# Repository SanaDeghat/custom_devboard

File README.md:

# custom_devboard

what? I made a devboard, which I creativly named devboard hehehhe

Why? My friend really insisted i learn how to lol, and also i rly wnat mroe jellycats so i gotta WORK yk??

How? I used Kicad, Did everything from the PCB to schematics all of it and i drew with clip studio paint (look in my devlog for details) 

What you struggled with and what you learned? OMG I LEARNED TAHT U CAN USE THE FILLY THING TO CONNECT STUFF (Zone fill) I think i would have had a mental breakdown if I had to connect all the GDN.

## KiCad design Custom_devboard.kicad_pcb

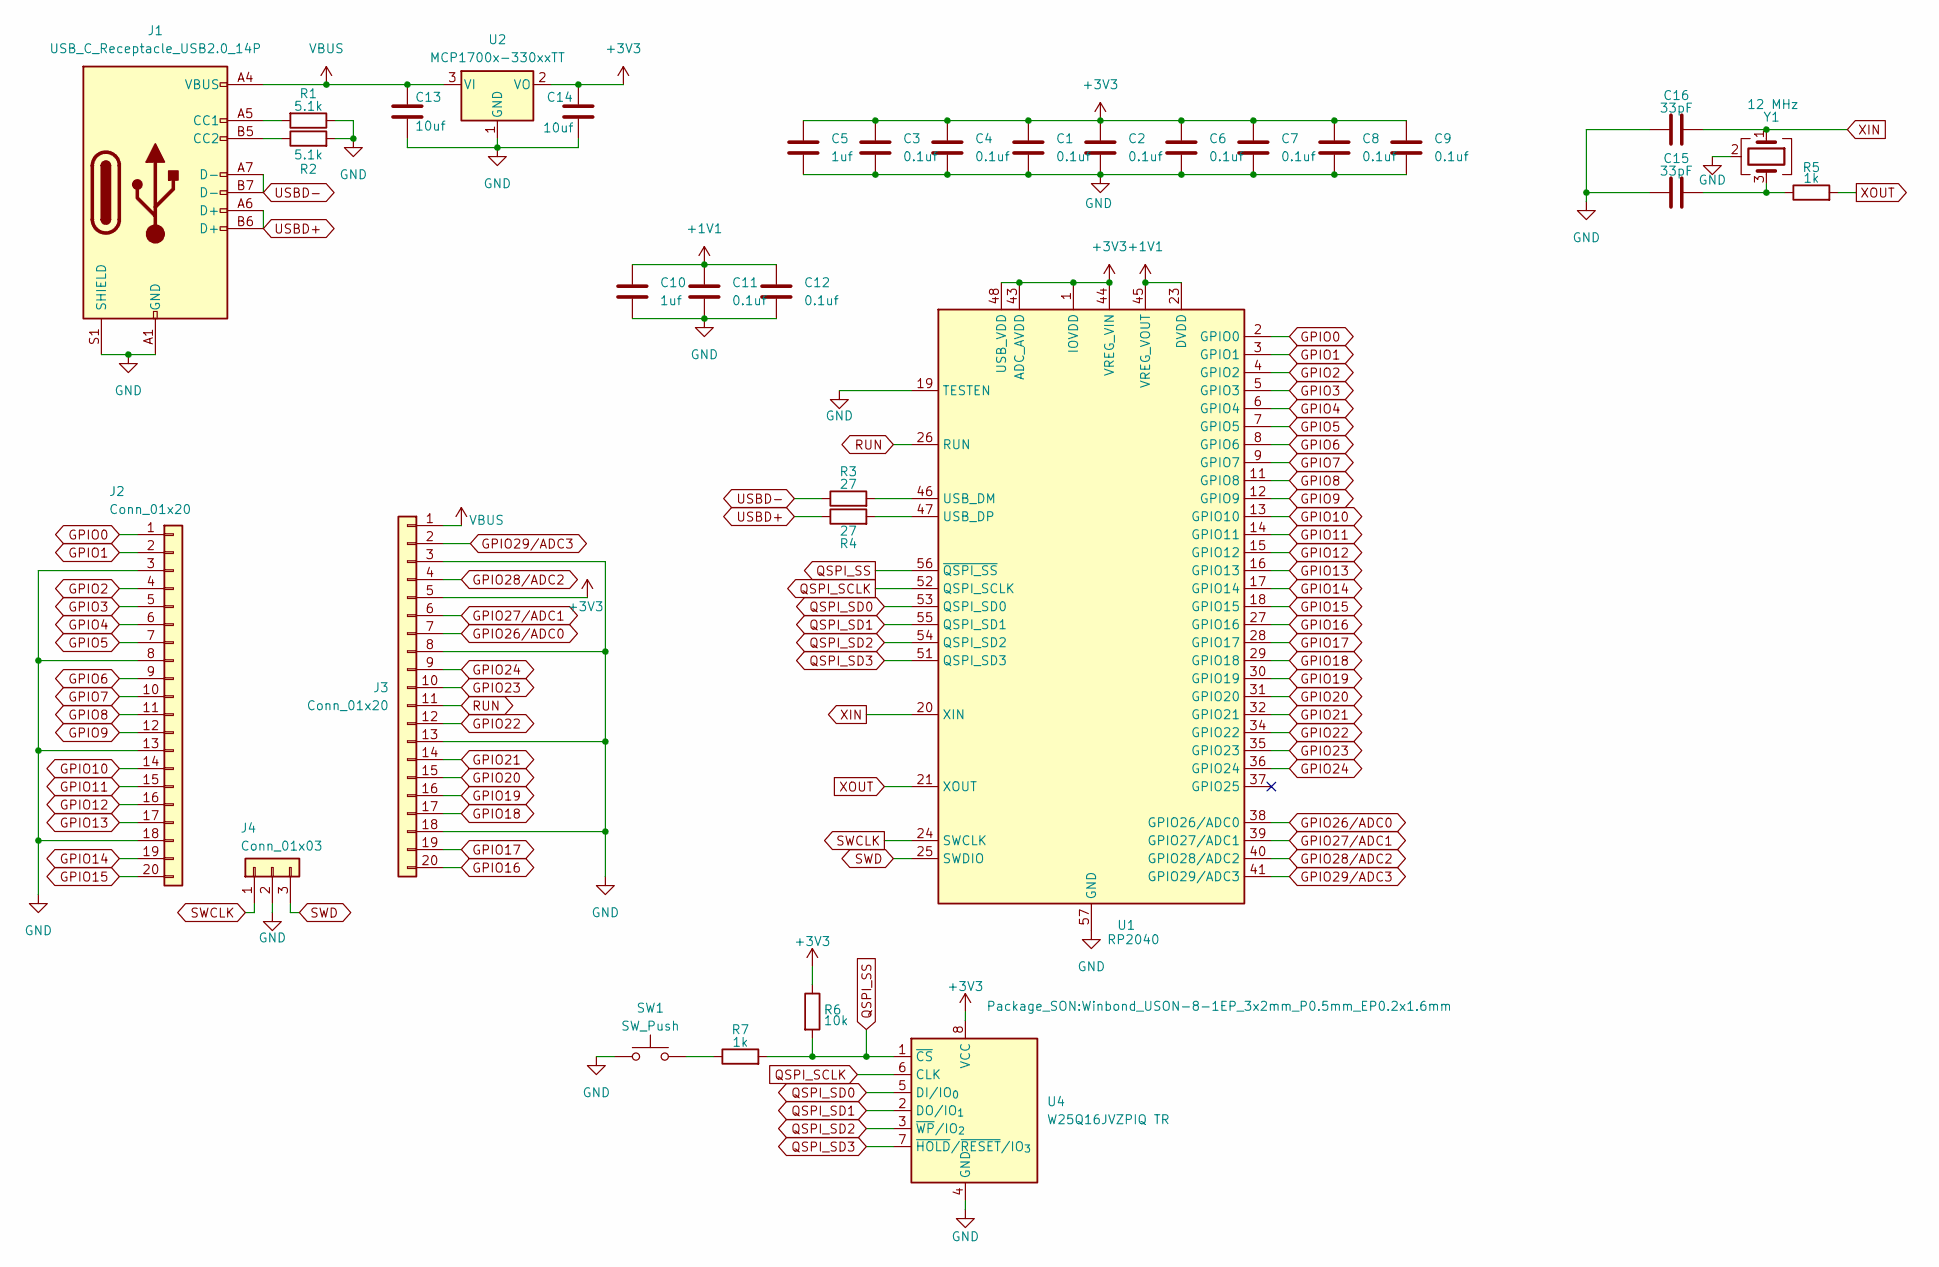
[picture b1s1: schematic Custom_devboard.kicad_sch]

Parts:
C1, C2, C3, C4, C6, C7, C8, C9, C11: 0.1uf; C_0402_1005Metric
C5, C10: 1uf; C_0402_1005Metric
C12: 0.1uf; C_0201_0603Metric
C13, C14: 10uf; C_0201_0603Metric
C15, C16: 33pF; C_0201_0603Metric
J1: USB_C_Receptacle_USB2.0_14P; USB_C_Receptacle_HRO_TYPE-C-31-M-12
J2, J3: Conn_01x20; PinHeader_1x20_P2.54mm_Vertical
J4: Conn_01x03; PinHeader_1x03_P2.54mm_Vertical
R1, R2: 5.1k; R_0402_1005Metric
R3, R4: 27; R_0402_1005Metric
R5, R7: 1k; R_0402_1005Metric
R6: 10k; R_0402_1005Metric
SW1: SW_Push; SW_Push_SPST_NO_Alps_SKRK
U1: RP2040; QFN-56-1EP_7x7mm_P0.4mm_EP3.2x3.2mm
U2: MCP1700x-330xxTT; SOT-23
U4: W25Q16JVZPIQ TR; Winbond_USON-8-1EP_3x2mm_P0.5mm_EP0.2x1.6mm
Y1: 12 MHz; Crystal_SMD_3225-4Pin_3.2x2.5mm

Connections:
+1V1: C10.1, C11.1, C12.1, U1.23 (DVDD), U1.45 (VREG_VOUT), U1.50 (DVDD)
+3V3: C1.1, C2.1, C3.1, C4.1, C5.1, C6.1, C7.1, C8.1, C9.1, C14.1, J3.5, R6.1, U1.1 (IOVDD), U1.10 (IOVDD), U1.22 (IOVDD), U1.33 (IOVDD), U1.42 (IOVDD), U1.43 (ADC_AVDD), U1.44 (VREG_VIN), U1.48 (USB_VDD), U1.49 (IOVDD), U2.2 (VO), U4.8 (VCC)
GND: C1.2, C2.2, C3.2, C4.2, C5.2, C6.2, C7.2, C8.2, C9.2, C10.2, C11.2, C12.2, C13.2, C14.2, C15.1, C16.1, J1.A1 (GND), J1.A12 (GND), J1.B1 (GND), J1.B12 (GND), J1.S1 (SHIELD), J2.3, J2.8, J2.13, J2.18, J3.3, J3.8, J3.13, J3.18, J4.2, R1.1, R2.2, SW1.1, U1.19 (TESTEN), U1.57 (GND), U2.1 (GND), U4.4 (GND), Y1.2 (G), Y1.4 (G)
GPIO0: J2.1, U1.2 (GPIO0)
GPIO1: J2.2, U1.3 (GPIO1)
GPIO2: J2.4, U1.4 (GPIO2)
GPIO3: J2.5, U1.5 (GPIO3)
GPIO4: J2.6, U1.6 (GPIO4)
GPIO5: J2.7, U1.7 (GPIO5)
GPIO6: J2.9, U1.8 (GPIO6)
GPIO7: J2.10, U1.9 (GPIO7)
GPIO8: J2.11, U1.11 (GPIO8)
GPIO9: J2.12, U1.12 (GPIO9)
GPIO10: J2.14, U1.13 (GPIO10)
GPIO11: J2.15, U1.14 (GPIO11)
GPIO12: J2.16, U1.15 (GPIO12)
GPIO13: J2.17, U1.16 (GPIO13)
GPIO14: J2.19, U1.17 (GPIO14)
GPIO15: J2.20, U1.18 (GPIO15)
GPIO16: J3.20, U1.27 (GPIO16)
GPIO17: J3.19, U1.28 (GPIO17)
GPIO18: J3.17, U1.29 (GPIO18)
GPIO19: J3.16, U1.30 (GPIO19)
GPIO20: J3.15, U1.31 (GPIO20)
GPIO21: J3.14, U1.32 (GPIO21)
GPIO22: J3.12, U1.34 (GPIO22)
GPIO23: J3.10, U1.35 (GPIO23)
GPIO24: J3.9, U1.36 (GPIO24)
GPIO26/ADC0: J3.7, U1.38 (GPIO26/ADC0)
GPIO27/ADC1: J3.6, U1.39 (GPIO27/ADC1)
GPIO28/ADC2: J3.4, U1.40 (GPIO28/ADC2)
GPIO29/ADC3: J3.2, U1.41 (GPIO29/ADC3)
unnamed: C15.2, R5.1, Y1.3
unnamed: J1.A5 (CC1), R1.2
unnamed: J1.B5 (CC2), R2.1
unnamed: R7.1, SW1.2
unnamed: R3.2, U1.46 (USB_DM)
unnamed: R4.2, U1.47 (USB_DP)
QSPI_SCLK: U1.52 (QSPI_SCLK), U4.6 (CLK)
QSPI_SD0: U1.53 (QSPI_SD0), U4.5 (DI/IO_{0})
QSPI_SD1: U1.55 (QSPI_SD1), U4.2 (DO/IO_{1})
QSPI_SD2: U1.54 (QSPI_SD2), U4.3 (~WP/IO_{2})
QSPI_SD3: U1.51 (QSPI_SD3), U4.7 (~HOLD/~RESET/IO_{3})
QSPI_SS: R6.2, R7.2, U1.56 (~QSPI_SS), U4.1 (~CS)
RUN: J3.11, U1.26 (RUN)
SWCLK: J4.1, U1.24 (SWCLK)
SWD: J4.3, U1.25 (SWDIO)
USBD+: J1.A6 (D+), J1.B6 (D+), R4.1
USBD-: J1.A7 (D-), J1.B7 (D-), R3.1
VBUS: C13.1, J1.A4 (VBUS), J1.A9 (VBUS), J1.B4 (VBUS), J1.B9 (VBUS), J3.1, U2.3 (VI)
XIN: C16.2, U1.20 (XIN), Y1.1
XOUT: R5.2, U1.21 (XOUT)

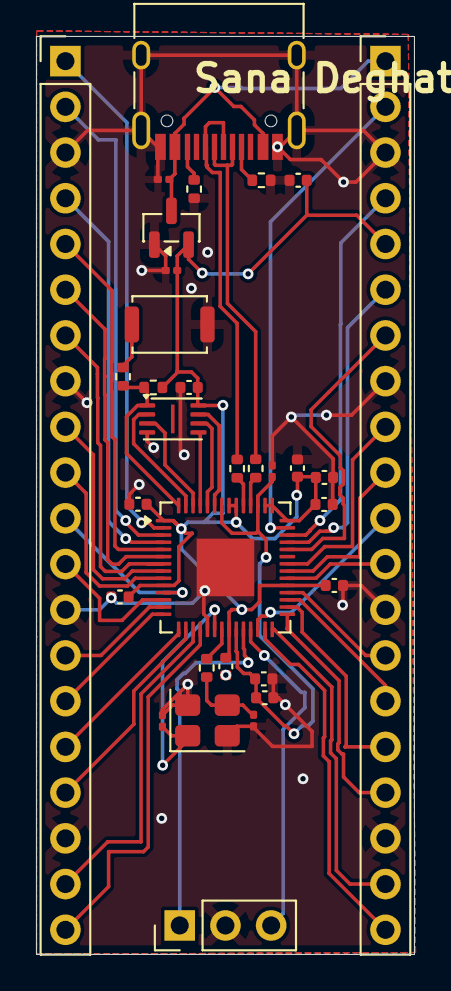
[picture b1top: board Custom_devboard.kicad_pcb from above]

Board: 2 copper layers, 21.0 x 51.0 mm, 32 parts (0 on the bottom side), 52 nets.

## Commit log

2026-03-29 Designing the schematic for the devboard
2026-03-29 Add first entry to Devlog with project details
2026-03-29 footprint complete and ERC
2026-03-29 Working on PCB (just placing everyhting)
2026-03-29 PCB, CONECTING EVERYHTING SUCKS SO BAD
2026-03-29 pcbcpcbcpcbcPCB
2026-03-30 drew silkscreen
2026-03-30 ALL the pcb beside the GND is done
2026-03-30 GND and DRC
2026-03-30 SilkScreen is done
2026-03-30 Update Devlog with new entries and details
    Added multiple devlog entries detailing schematic design, PCB work, and silkscreen drawing.
2026-03-30 final btw
